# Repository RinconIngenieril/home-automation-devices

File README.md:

# Home Automation Devices

Several Open Hardware electronics devices based in the SoC ESP8266 for Home Automation.

AC-Relay https://github.com/kikeelectronico/ac-relay

Ceiling lamp https://github.com/kikeelectronico/ceiling-lamp

RGB Controller https://github.com/kikeelectronico/rgb-strip-controller

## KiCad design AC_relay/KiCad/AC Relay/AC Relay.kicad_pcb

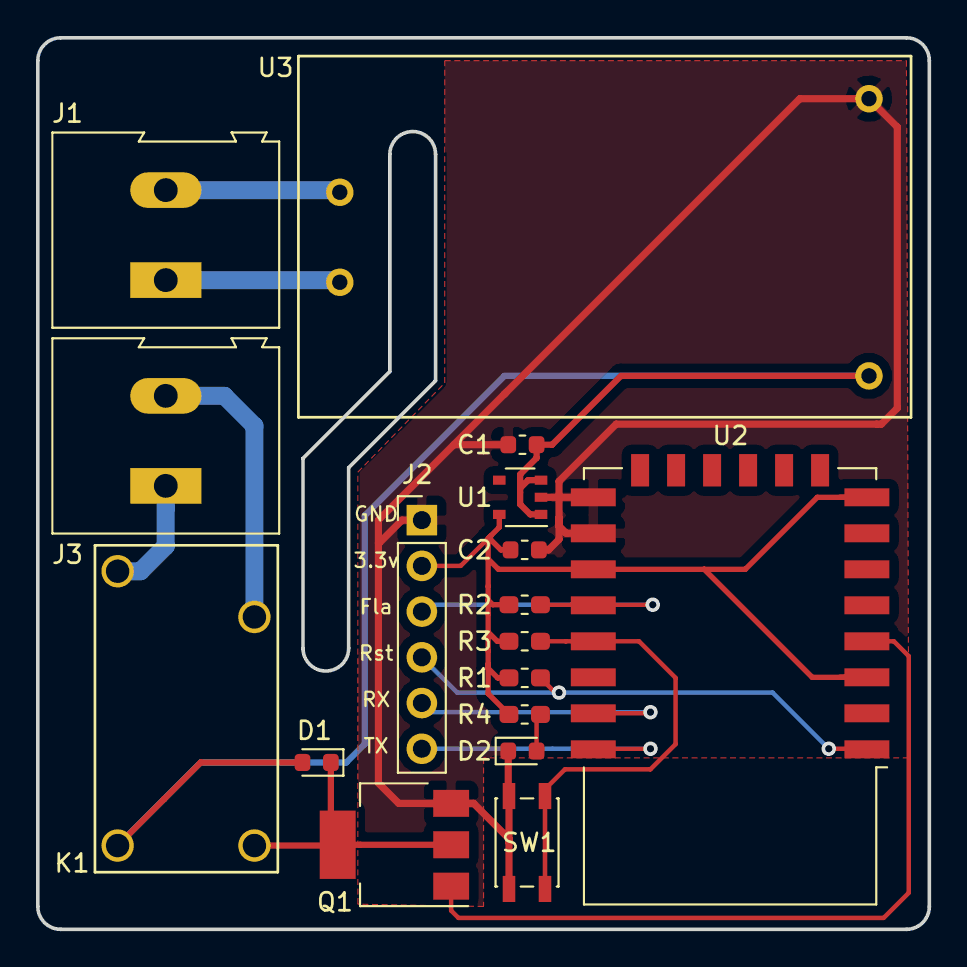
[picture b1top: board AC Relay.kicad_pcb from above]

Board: 2 copper layers, 49.5 x 49.5 mm, 17 parts (0 on the bottom side), 15 nets.

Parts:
C1, C2: 0.47uF; C_0603_1608Metric
D1: RGF1B; D_0603_1608Metric
D2: LED_verde; LED_0603_1608Metric
J1, J3: Screw_Terminal_01x02; TerminalBlock_Altech_AK300-2_P5.00mm
J2: Conn_01x06_Female; PinHeader_1x06_P2.54mm_Vertical
K1: 1461492-2; Rele-1461492-2
Q1: FDN537N; SOT-223
R1, R2, R3: 10k; R_0603_1608Metric_Pad1.05x0.95mm_HandSolder
R4: 82.5; R_0603_1608Metric_Pad1.05x0.95mm_HandSolder
SW1: SW_Push; SW_SPST_EVQP2
U1: BU33SD5WG-TR; TSOP-5_1.65x3.05mm_P0.95mm
U2: ESP-12E
U3: HLK-PM01

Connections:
+3V3: C2.1, J2.2, R1.2, R2.1, R3.2, R4.2, U1.5, U2.3, U2.8, U2.17
+5V: C1.1, D1.2, K1.2, U1.1, U1.3, U3.4
/Button: R3.1, SW1.1, U2.19
/Flash: J2.3, R2.2, U2.18
/RX: J2.5, U2.21
/Relay: Q1.1, U2.4
/Rst: J2.4, R1.1, U2.1
/TX: J2.6, U2.22
GND: C1.2, C2.2, D2.1, J2.1, Q1.3, SW1.2, U1.2, U2.15, U2.16, U3.3
unnamed: D1.1, K1.1, Q1.2, Q1.4
unnamed: D2.2, R4.1
unnamed: J1.1, U3.2
unnamed: J1.2, U3.1
unnamed: J3.1, K1.3
unnamed: J3.2, K1.4

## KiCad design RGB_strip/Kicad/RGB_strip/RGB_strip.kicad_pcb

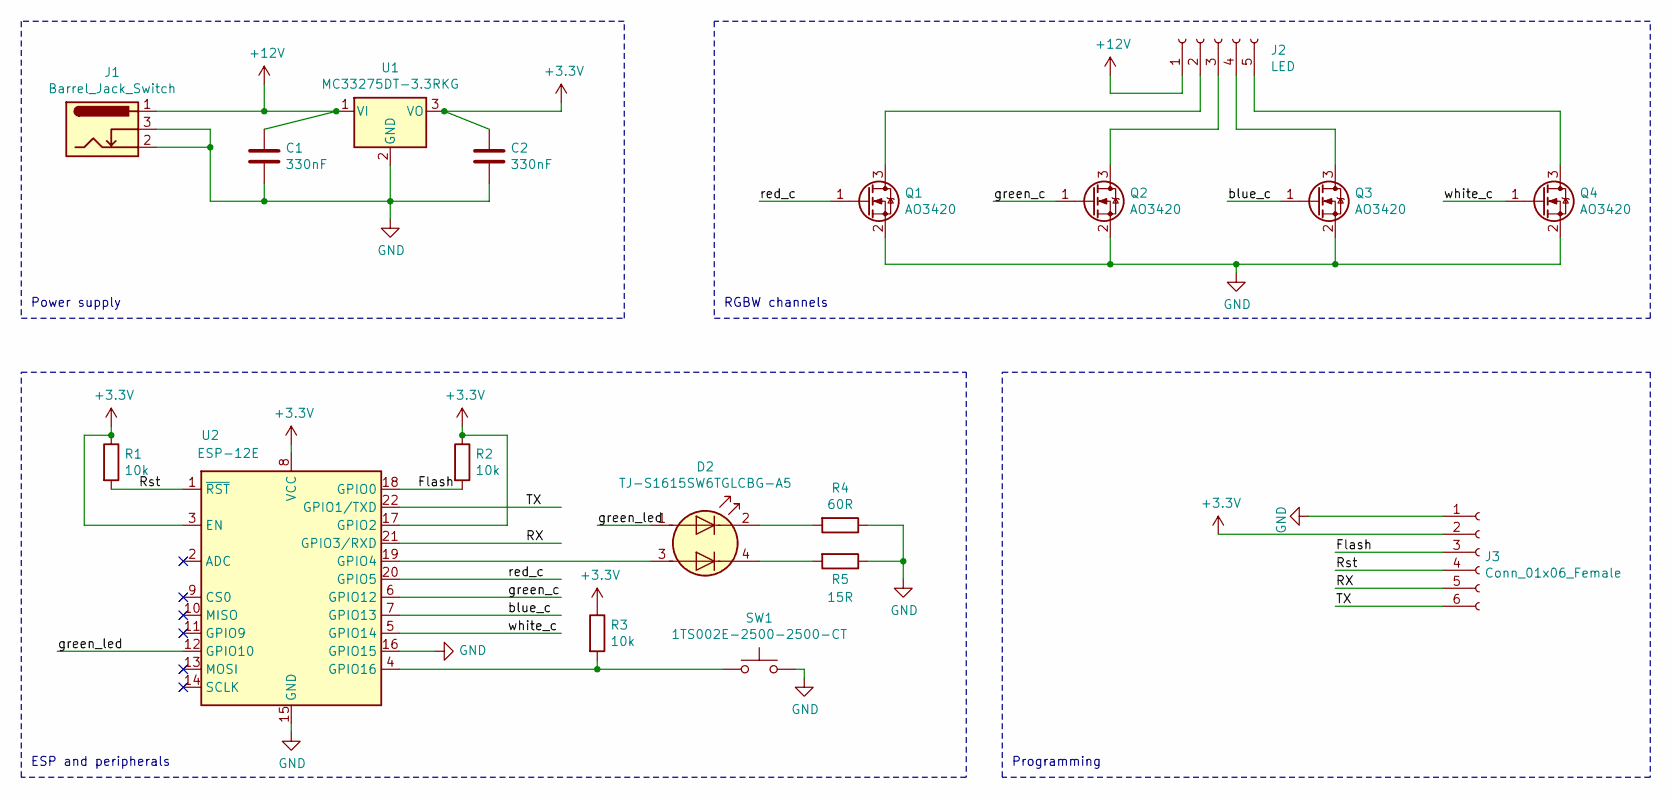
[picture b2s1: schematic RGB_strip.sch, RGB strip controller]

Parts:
C1, C2: 330nF; C_0603_1608Metric
D2: TJ-S1615SW6TGLCBG-A5
J1: Barrel_Jack_Switch; BarrelJack_Wuerth_6941xx301002
J2: LED; Molex_KK-254_AE-6410-05A_1x05_P2.54mm_Vertical
J3: Conn_01x06_Female; Molex_KK-254_AE-6410-06A_1x06_P2.54mm_Vertical
Q1, Q2, Q3, Q4: AO3420; SOT-23
R1, R2, R3: 10k; R_0603_1608Metric_Pad1.05x0.95mm_HandSolder
R4: 60R; R_0603_1608Metric_Pad1.05x0.95mm_HandSolder
R5: 15R; R_0603_1608Metric_Pad1.05x0.95mm_HandSolder
SW1: 1TS002E-2500-2500-CT; SW_SPST_CK_RS282G05A3
U1: MC33275DT-3.3RKG; TO-252-2
U2: ESP-12E

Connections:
+3V3: C2.1, J3.2, R1.1, R2.1, R3.1, U1.3 (VO), U2.3 (EN), U2.8 (VCC), U2.17 (GPIO2)
+12V: C1.1, J1.1, J2.1, U1.1 (VI)
/Flash: J3.3, R2.2, U2.18 (GPIO0)
/RX: J3.5, U2.21 (GPIO3/RXD)
/Rst: J3.4, R1.2, U2.1 (~RST)
/TX: J3.6, U2.22 (GPIO1/TXD)
/blue_c: Q3.1 (G), U2.7 (GPIO13)
/green_c: Q2.1 (G), U2.6 (GPIO12)
/green_led: D2.1 (A1), U2.12 (GPIO10)
/red_c: Q1.1 (G), U2.20 (GPIO5)
/white_c: Q4.1 (G), U2.5 (GPIO14)
GND: C1.2, C2.2, J1.2, J1.3, J3.1, Q1.2 (S), Q2.2 (S), Q3.2 (S), Q4.2 (S), R4.1, R5.1, SW1.2, U1.2 (GND), U2.15 (GND), U2.16 (GPIO15)
unnamed: D2.2 (K1), R4.2
unnamed: D2.3 (A2), U2.19 (GPIO4)
unnamed: D2.4 (K2), R5.2
unnamed: J2.2, Q1.3 (D)
unnamed: J2.3, Q2.3 (D)
unnamed: J2.4, Q3.3 (D)
unnamed: J2.5, Q4.3 (D)
unnamed: R3.2, SW1.1, U2.4 (GPIO16)

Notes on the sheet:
Power supply
RGBW channels
ESP and peripherals
Programming

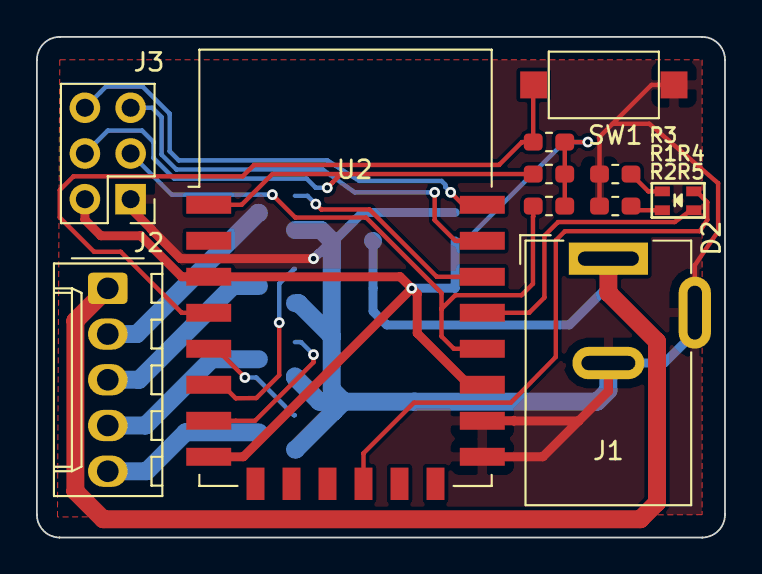
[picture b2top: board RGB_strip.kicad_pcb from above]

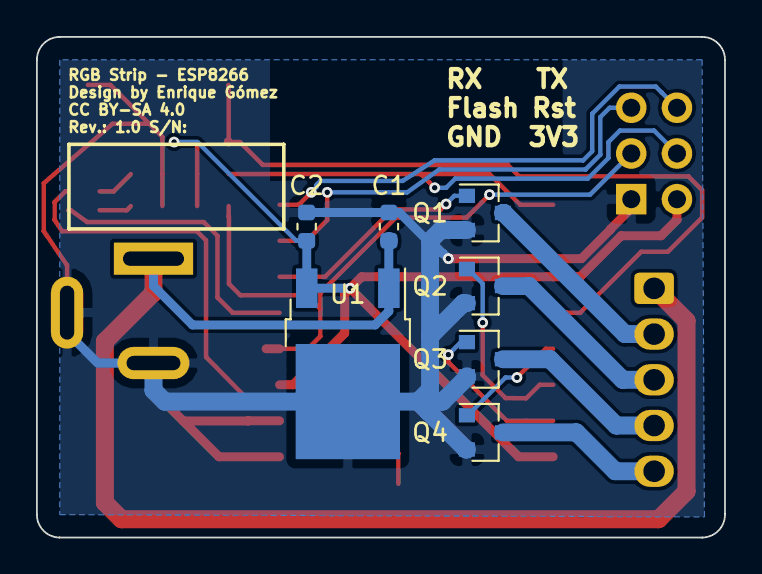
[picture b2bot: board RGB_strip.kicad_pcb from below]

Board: 2 copper layers, 38.2 x 27.8 mm, 18 parts (7 on the bottom side), 20 nets.

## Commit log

2019-03-01 Image and readme update
2019-03-01 Playing with readme
2019-03-08 Test firmware
2019-03-08 Readme update
2019-03-09 DOC and firmware finished
2019-03-09 README
2019-03-09 README test
2019-03-09 README test 2
2019-03-23 Diode footprint fised
2020-04-14 Celling lamp & RGB strip controller
2020-11-15 RGB controller 3D enclosure

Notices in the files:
AC_relay/KiCad/AC Relay/AC Relay.kicad_pcb:
CC BY-SA 4.0
